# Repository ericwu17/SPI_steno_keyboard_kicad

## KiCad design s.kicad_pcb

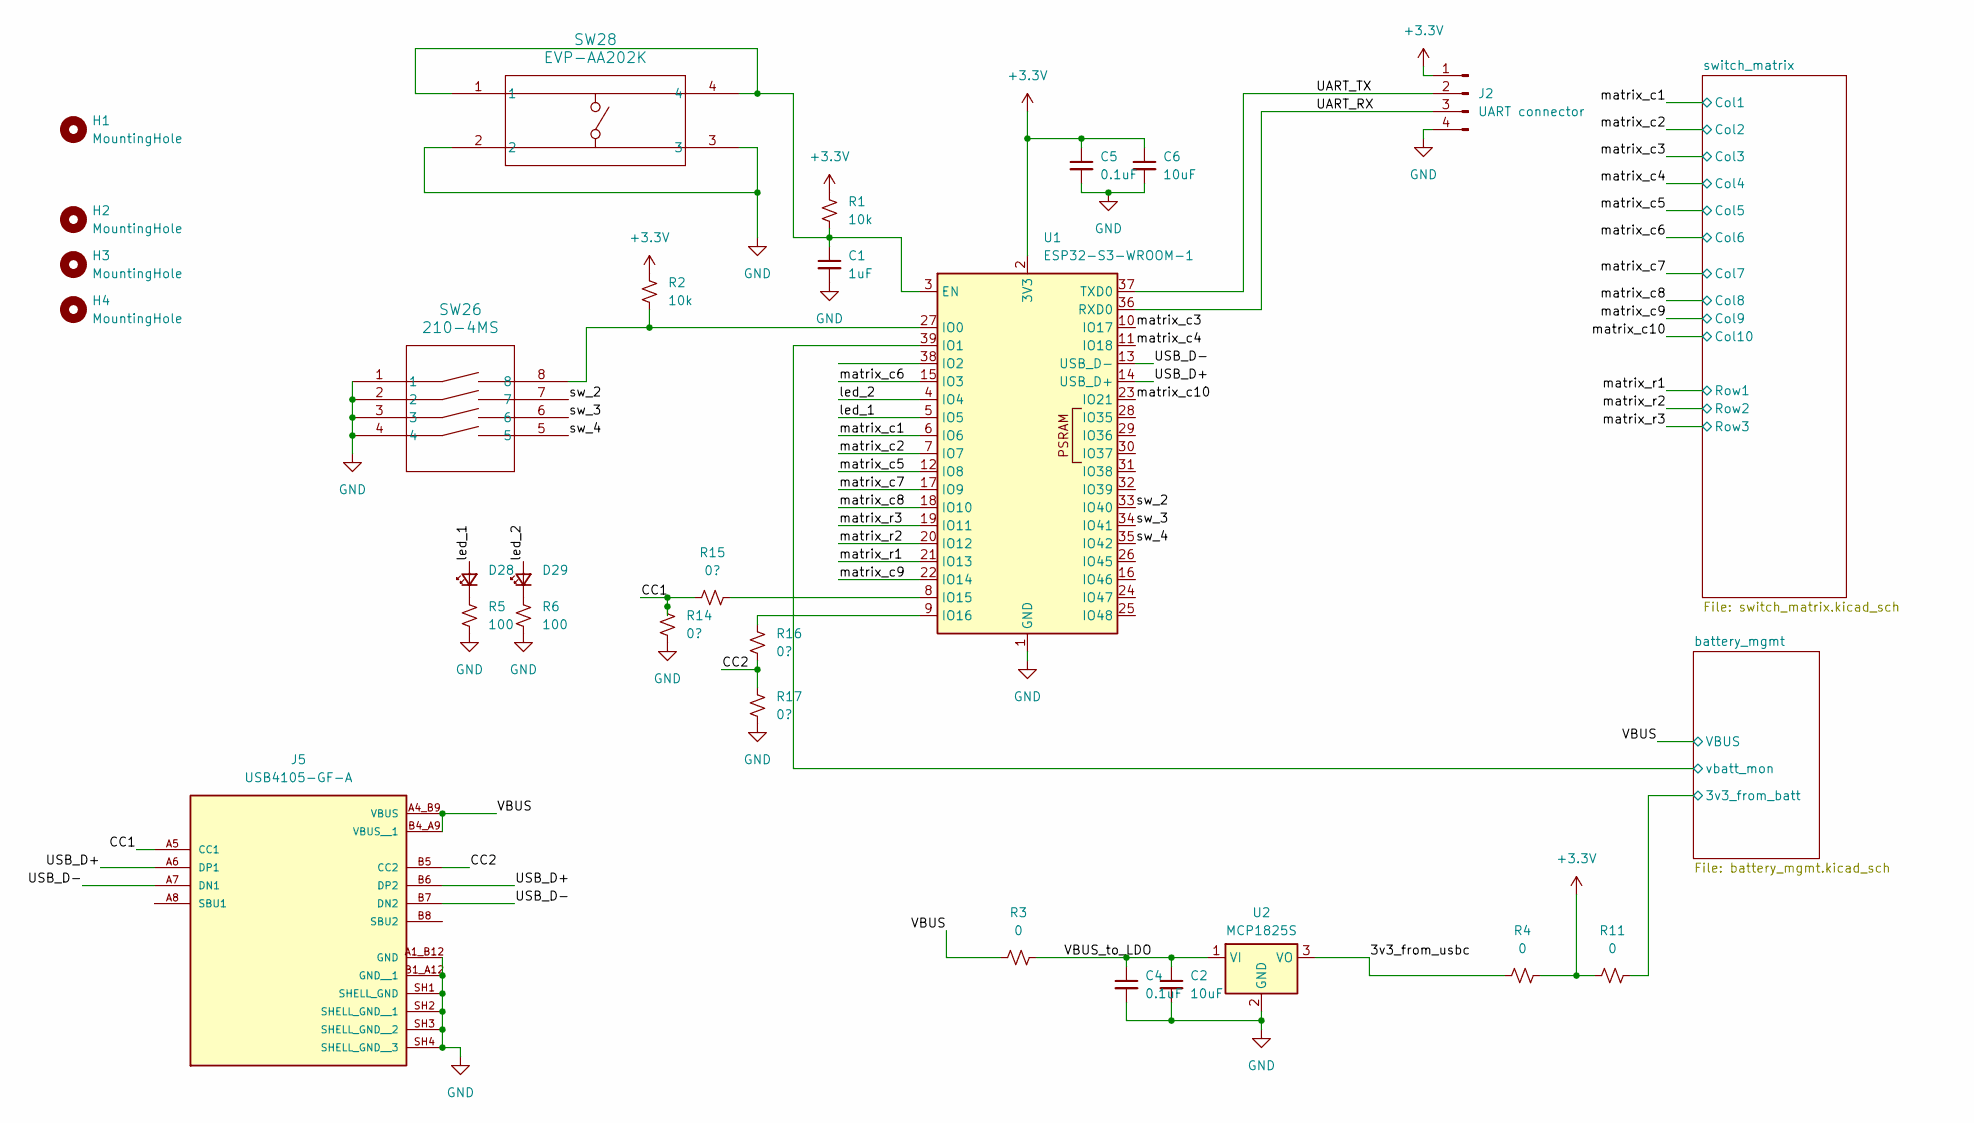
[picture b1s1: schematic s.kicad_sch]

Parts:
C1: 1uF; C_0805_2012Metric_Pad1.18x1.45mm_HandSolder
C2, C6: 10uF; C_0805_2012Metric_Pad1.18x1.45mm_HandSolder
C4, C5: 0.1uF; C_0805_2012Metric_Pad1.18x1.45mm_HandSolder
D28, D29: LED_0805_2012Metric_Pad1.15x1.40mm_HandSolder
H1, H2, H3, H4: MountingHole; MountingHole_3mm
J2: UART connector; PinHeader_1x04_P2.54mm_Vertical
J5: USB4105-GF-A; GCT_USB4105-GF-A; PARTREV B4
R1, R2: 10k; R_0805_2012Metric_Pad1.20x1.40mm_HandSolder
R3, R4, R11: 0; R_0805_2012Metric_Pad1.20x1.40mm_HandSolder
R5, R6: 100; R_0805_2012Metric_Pad1.20x1.40mm_HandSolder
R14, R15, R16, R17: 0?; R_0805_2012Metric_Pad1.20x1.40mm_HandSolder
SW26: 210-4MS; DIP8_210-4_CTS
SW28: EVP-AA202K; SW_EVP-AA102K_PAN
U1: ESP32-S3-WROOM-1
U2: MCP1825S; SOT-223-3_TabPin2

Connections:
+3.3V: C5.1, C6.1, J2.1, R1.1, R2.1, R4.2, R11.1, U1.2 (3V3)
/3v3_from_usbc: R4.1, U2.3 (VO)
/CC1: J5.A5 (CC1), R14.1, R15.1
/CC2: J5.B5 (CC2), R16.1, R17.1
/UART_RX: J2.3, U1.36 (RXD0)
/UART_TX: J2.2, U1.37 (TXD0)
/USB_D+: J5.A6 (DP1), J5.B6 (DP2), U1.14 (USB_D+)
/USB_D-: J5.A7 (DN1), J5.B7 (DN2), U1.13 (USB_D-)
/VBUS: J5.A4_B9 (VBUS), J5.B4_A9 (VBUS__1), R3.1; also elsewhere on the board
/VBUS_to_LDO: C2.1, C4.1, R3.2, U2.1 (VI)
/battery_mgmt/3v3_from_batt: R11.2; also elsewhere on the board
/battery_mgmt/vbatt_mon: U1.39 (IO1); also elsewhere on the board
/led_1: D28.2 (A), U1.5 (IO5)
/led_2: D29.2 (A), U1.4 (IO4)
/matrix_c1: U1.6 (IO6); also elsewhere on the board
/matrix_c2: U1.7 (IO7); also elsewhere on the board
/matrix_c3: U1.10 (IO17); also elsewhere on the board
/matrix_c4: U1.11 (IO18); also elsewhere on the board
/matrix_c5: U1.12 (IO8); also elsewhere on the board
/matrix_c6: U1.15 (IO3); also elsewhere on the board
/matrix_c7: U1.17 (IO9); also elsewhere on the board
/matrix_c8: U1.18 (IO10); also elsewhere on the board
/matrix_c9: U1.22 (IO14); also elsewhere on the board
/matrix_c10: U1.23 (IO21); also elsewhere on the board
/matrix_r1: U1.21 (IO13); also elsewhere on the board
/matrix_r2: U1.20 (IO12); also elsewhere on the board
/matrix_r3: U1.19 (IO11); also elsewhere on the board
/sw_2: SW26.7, U1.33 (IO40)
/sw_3: SW26.6, U1.34 (IO41)
/sw_4: SW26.5, U1.35 (IO42)
GND: C1.2, C2.2, C4.2, C5.2, C6.2, J2.4, J5.A1_B12 (GND), J5.B1_A12 (GND__1), J5.SH1 (SHELL_GND), J5.SH2 (SHELL_GND__1), J5.SH3 (SHELL_GND__2), J5.SH4 (SHELL_GND__3), R5.2, R6.2, R14.2, R17.2, SW26.1, SW26.2, SW26.3, SW26.4, SW28.2, SW28.3, U1.1 (GND), U1.40 (GND), U1.41 (GND), U2.2 (GND); also elsewhere on the board
unnamed: D28.1 (K), R5.1
unnamed: D29.1 (K), R6.1
unnamed: C1.1, R1.2, SW28.1, SW28.4, U1.3 (EN)
unnamed: R2.2, SW26.8, U1.27 (IO0)
unnamed: R15.2, U1.8 (IO15)
unnamed: R16.2, U1.9 (IO16)

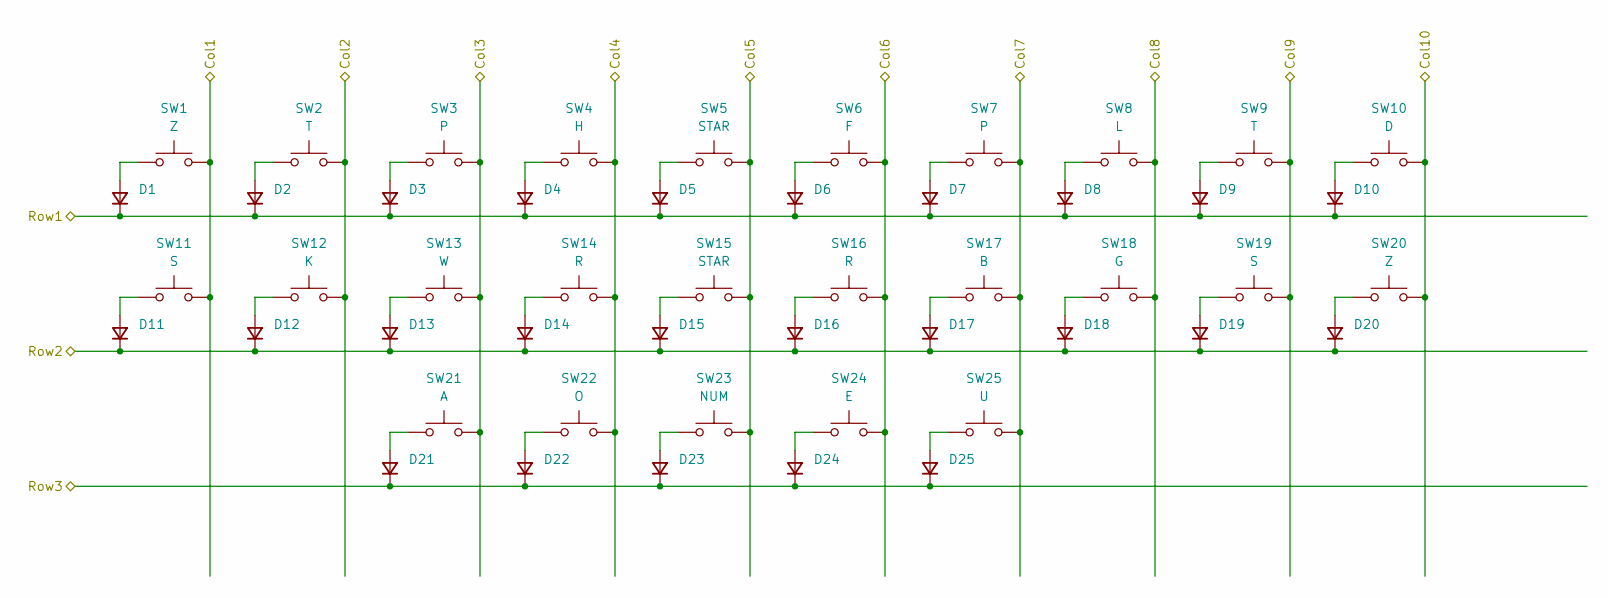
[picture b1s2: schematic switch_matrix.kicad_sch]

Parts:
D1, D2, D3, D4, D5, D6, D7, D8, D9, D10, D11, D12, D13, D14, D15, D16, D17, D18, D19, D20, D21, D22, D23, D24, D25: D_SOD-323_HandSoldering
SW1, SW20: Z; SW_Kailh_Choc_V1_THT
SW2, SW9: T; SW_Kailh_Choc_V1_THT
SW3, SW7: P; SW_Kailh_Choc_V1_THT
SW4: H; SW_Kailh_Choc_V1_THT
SW5, SW15: STAR; SW_Kailh_Choc_V1_THT
SW6: F; SW_Kailh_Choc_V1_THT
SW8: L; SW_Kailh_Choc_V1_THT
SW10: D; SW_Kailh_Choc_V1_THT
SW11, SW19: S; SW_Kailh_Choc_V1_THT
SW12: K; SW_Kailh_Choc_V1_THT
SW13: W; SW_Kailh_Choc_V1_THT
SW14, SW16: R; SW_Kailh_Choc_V1_THT
SW17: B; SW_Kailh_Choc_V1_THT
SW18: G; SW_Kailh_Choc_V1_THT
SW21: A; SW_Kailh_Choc_V1_THT
SW22: O; SW_Kailh_Choc_V1_THT
SW23: NUM; SW_Kailh_Choc_V1_THT
SW24: E; SW_Kailh_Choc_V1_THT
SW25: U; SW_Kailh_Choc_V1_THT

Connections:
/matrix_c1: SW1.2, SW11.2; also elsewhere on the board
/matrix_c2: SW2.2, SW12.2; also elsewhere on the board
/matrix_c3: SW3.2, SW13.2, SW21.2; also elsewhere on the board
/matrix_c4: SW4.2, SW14.2, SW22.2; also elsewhere on the board
/matrix_c5: SW5.2, SW15.2, SW23.2; also elsewhere on the board
/matrix_c6: SW6.2, SW16.2, SW24.2; also elsewhere on the board
/matrix_c7: SW7.2, SW17.2, SW25.2; also elsewhere on the board
/matrix_c8: SW8.2, SW18.2; also elsewhere on the board
/matrix_c9: SW9.2, SW19.2; also elsewhere on the board
/matrix_c10: SW10.2, SW20.2; also elsewhere on the board
/matrix_r1: D1.1 (K), D2.1 (K), D3.1 (K), D4.1 (K), D5.1 (K), D6.1 (K), D7.1 (K), D8.1 (K), D9.1 (K), D10.1 (K); also elsewhere on the board
/matrix_r2: D11.1 (K), D12.1 (K), D13.1 (K), D14.1 (K), D15.1 (K), D16.1 (K), D17.1 (K), D18.1 (K), D19.1 (K), D20.1 (K); also elsewhere on the board
/matrix_r3: D21.1 (K), D22.1 (K), D23.1 (K), D24.1 (K), D25.1 (K); also elsewhere on the board
unnamed: D1.2 (A), SW1.1
unnamed: D2.2 (A), SW2.1
unnamed: D3.2 (A), SW3.1
unnamed: D4.2 (A), SW4.1
unnamed: D5.2 (A), SW5.1
unnamed: D6.2 (A), SW6.1
unnamed: D7.2 (A), SW7.1
unnamed: D8.2 (A), SW8.1
unnamed: D9.2 (A), SW9.1
unnamed: D10.2 (A), SW10.1
unnamed: D11.2 (A), SW11.1
unnamed: D12.2 (A), SW12.1
unnamed: D13.2 (A), SW13.1
unnamed: D14.2 (A), SW14.1
unnamed: D15.2 (A), SW15.1
unnamed: D16.2 (A), SW16.1
unnamed: D17.2 (A), SW17.1
unnamed: D18.2 (A), SW18.1
unnamed: D19.2 (A), SW19.1
unnamed: D20.2 (A), SW20.1
unnamed: D21.2 (A), SW21.1
unnamed: D22.2 (A), SW22.1
unnamed: D23.2 (A), SW23.1
unnamed: D24.2 (A), SW24.1
unnamed: D25.2 (A), SW25.1

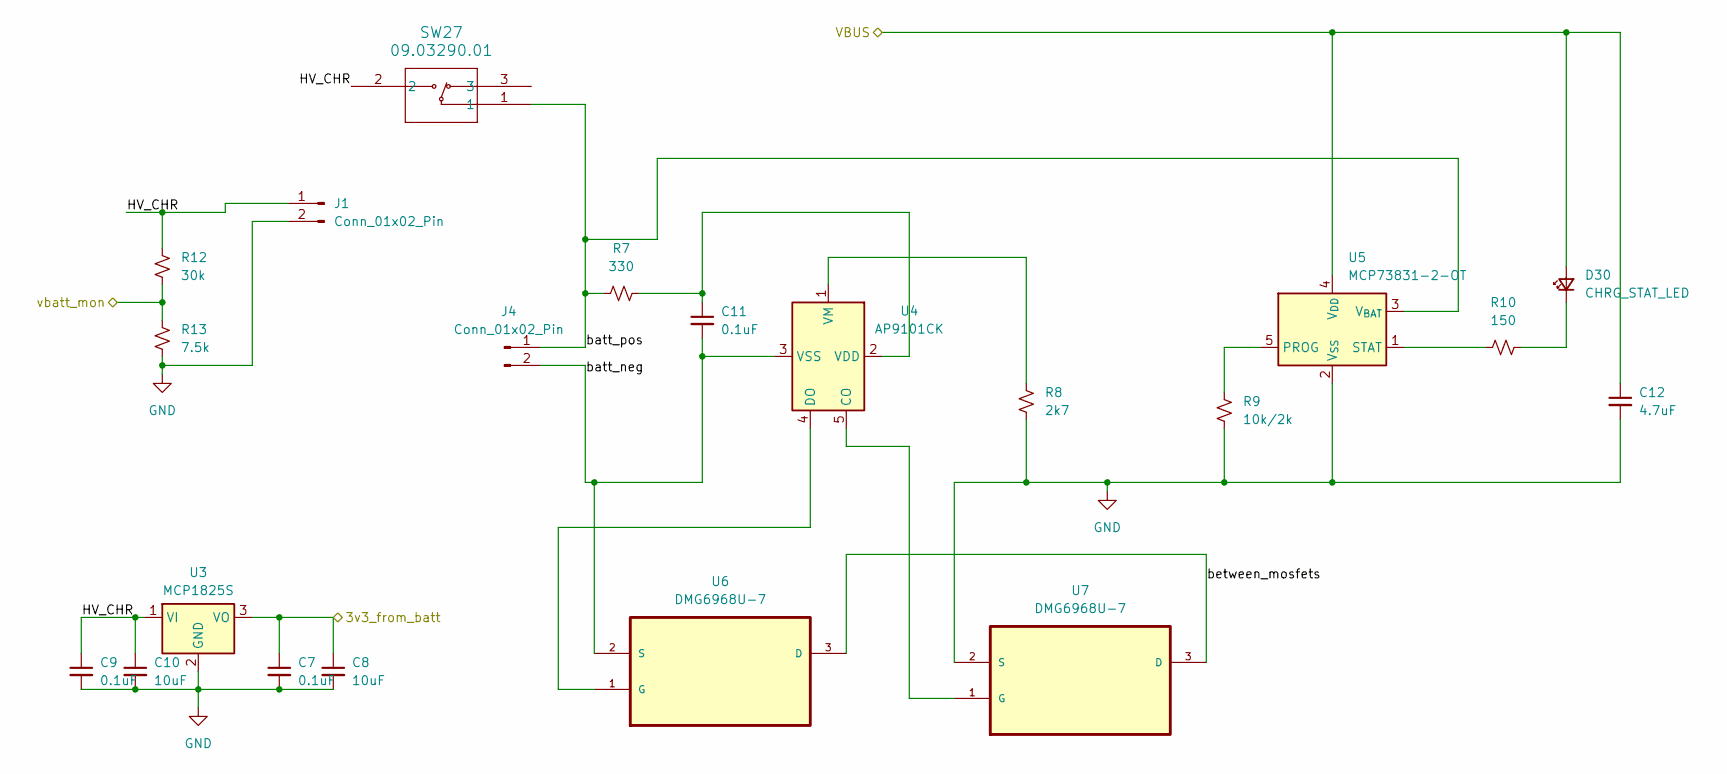
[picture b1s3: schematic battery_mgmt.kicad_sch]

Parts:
C7, C9, C11: 0.1uF; C_0805_2012Metric_Pad1.18x1.45mm_HandSolder
C8, C10: 10uF; C_0805_2012Metric_Pad1.18x1.45mm_HandSolder
C12: 4.7uF; C_0805_2012Metric_Pad1.18x1.45mm_HandSolder
D30: CHRG_STAT_LED; LED_0805_2012Metric_Pad1.15x1.40mm_HandSolder
J1: Conn_01x02_Pin; PinHeader_1x02_P2.54mm_Vertical
J4: Conn_01x02_Pin; JST_PH_S2B-PH-K_1x02_P2.00mm_Horizontal
R7: 330; R_0805_2012Metric_Pad1.20x1.40mm_HandSolder
R8: 2k7; R_0805_2012Metric_Pad1.20x1.40mm_HandSolder
R9: 10k/2k; R_0805_2012Metric_Pad1.20x1.40mm_HandSolder
R10: 150; R_0805_2012Metric_Pad1.20x1.40mm_HandSolder
R12: 30k; R_0805_2012Metric_Pad1.20x1.40mm_HandSolder
R13: 7.5k; R_0805_2012Metric_Pad1.20x1.40mm_HandSolder
SW27: 09.03290.01; 09.03290_EAO
U3: MCP1825S; SOT-223-3_TabPin2
U4: AP9101CK; SOT-23-5
U5: MCP73831-2-OT; SOT-23-5
U6, U7: DMG6968U-7; SOT95P240X110-3N; MPN DMG6968U-7

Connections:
/VBUS: C12.1, D30.2 (A), U5.4 (V_{DD}); also elsewhere on the board
/battery_mgmt/3v3_from_batt: C7.1, C8.1, U3.3 (VO); also elsewhere on the board
/battery_mgmt/HV_CHR: C9.1, C10.1, J1.1, R12.1, SW27.2, U3.1 (VI)
/battery_mgmt/batt_neg: C11.2, J4.2, U4.3 (VSS), U6.2 (S)
/battery_mgmt/batt_pos: J4.1, R7.1, SW27.1, U5.3 (V_{BAT})
/battery_mgmt/between_mosfets: U6.3 (D), U7.3 (D)
/battery_mgmt/vbatt_mon: R12.2, R13.1; also elsewhere on the board
GND: C7.2, C8.2, C9.2, C10.2, C12.2, J1.2, R8.2, R9.2, R13.2, U3.2 (GND), U5.2 (V_{SS}), U7.2 (S); also elsewhere on the board
unnamed: D30.1 (K), R10.2
unnamed: U4.5 (CO), U7.1 (G)
unnamed: U4.4 (DO), U6.1 (G)
unnamed: C11.1, R7.2, U4.2 (VDD)
unnamed: R8.1, U4.1 (VM)
unnamed: R9.1, U5.5 (PROG)
unnamed: R10.1, U5.1 (STAT)

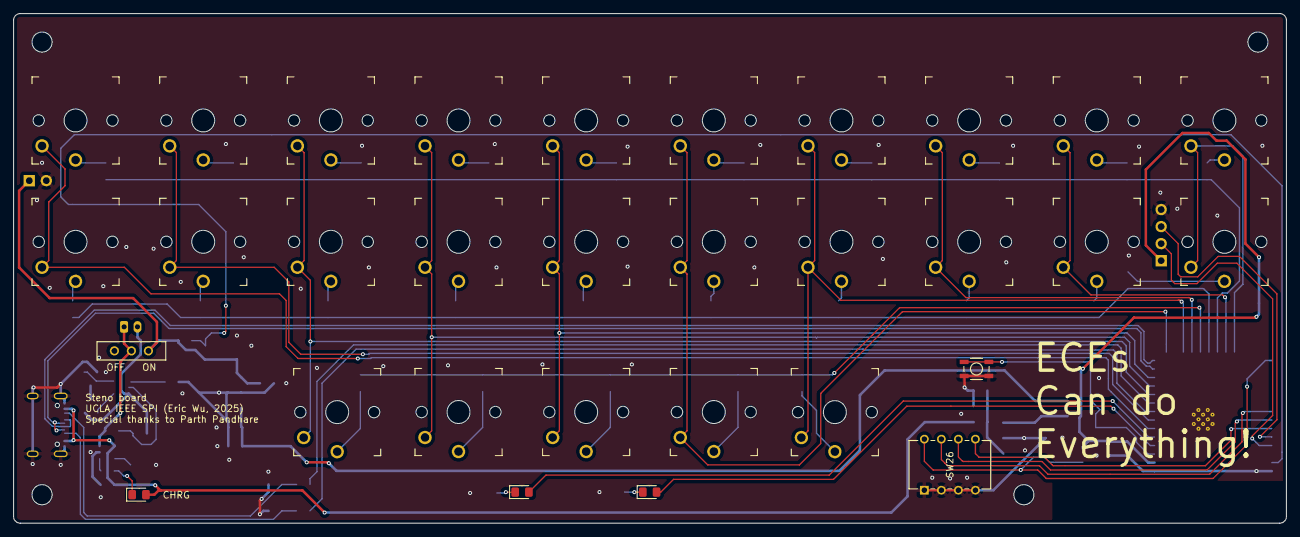
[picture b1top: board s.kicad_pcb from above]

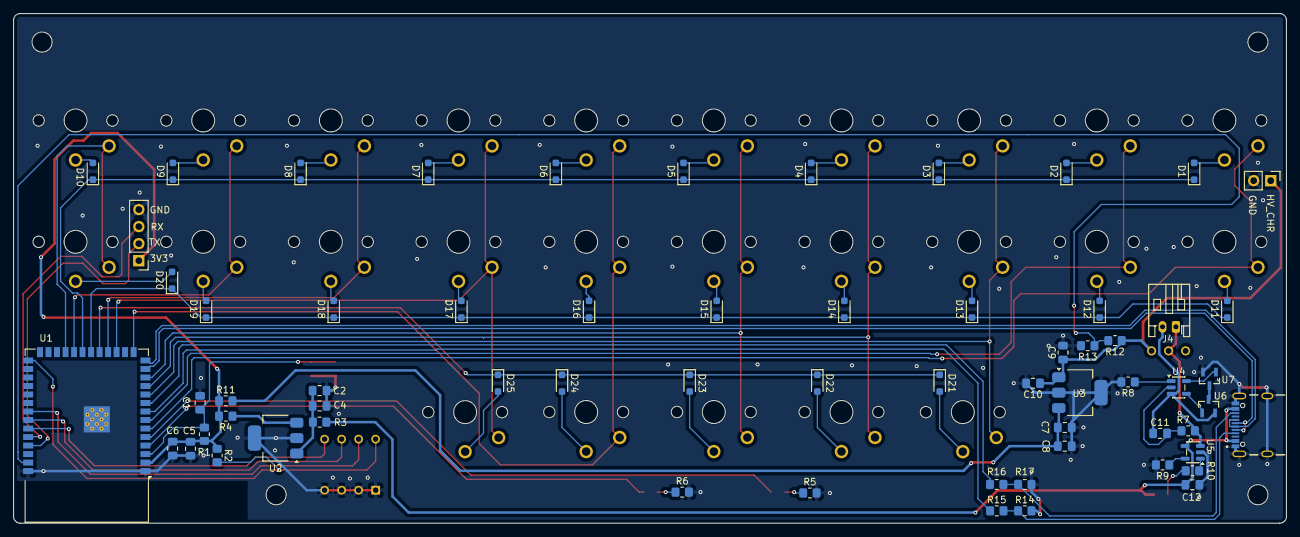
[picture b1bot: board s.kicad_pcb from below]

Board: 2 copper layers, 190.0 x 76.0 mm, 99 parts (64 on the bottom side), 73 nets.

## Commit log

2025-10-25 initial commit: added submodules
2025-10-25 initial commit 2: initialize project
2025-10-25 got basic MCU powering from USBC
2025-10-25 make key matrix
2025-10-25 rename backup, for somme reason
    idk why kicad did this
2025-10-25 connect MCU to matrix
2025-10-26 add supporting stuff and assigned footprints
2025-10-26 copied battery charging schematic
2025-10-26 update footprints
2025-10-26 move stuff around on pcb
2025-10-26 routed the key matrix
2025-10-26 quick commit: moved stuff around and deleted a capacitor
2025-10-26 route some more stuff
2025-10-26 route dip switches
2025-10-26 route battery charging stuff
2025-10-26 move stuff around (minor)
2025-10-27 add submodule for Kailh Choc V1 footprints
2025-10-27 change key footprints to kailh choc (PCB not fixed yet)
2025-10-27 remove 2 of the 4 user LEDs
2025-10-27 PCB cleanup remove old row/col traces
2025-10-28 route PCB with new keys and new key spacing
    key spacing done by hand
2025-10-28 add backups
2025-10-30 modify schematic: add switch between voltage regs
2025-10-30 work on PCB
2025-10-30 more work on PCB: routed grounds
2025-10-30 fix DRC violations and warnings
2025-11-01 use 0-ohm resistors, not switches, to control power source
2025-11-01 add a voltage divider for battery voltage monitoring
2025-11-06 make gap in PCB for antenna
2025-11-06 remove silkscreen from MCU component
2025-11-06 change min hole size to 0.2 mm
2025-11-06 some silk screen changes
2025-11-06 silk screen changes
2025-11-06 new usb port footprint
2025-11-07 change power switch
2025-11-07 minor edit to some traces
2025-11-07 add design rules from https://github.com/labtroll/KiCad-DesignRules
2025-11-07 update silk screen to confrom to design rules
2025-11-07 reroute board
2025-11-07 add planes for ground
2025-11-07 add 3 of 4 mounting holes
    still need to think about the last one...
2025-11-08 add the fourth mounting hole
2025-11-08 add a few vias
2025-11-13 add a push button for RST
2025-11-16 change footprint of JST connector. Vertical -> horizontal
2025-11-18 rename labels for mounting holes
2025-11-18 WIP: drafting PCB edges
2025-11-18 WIP :finalize edge cuts
    The new board dimensions are 189.95mm x 76.05mm
    with corners of radius 1.00 mm
2025-11-18 WIP: routing traces
2025-11-18 WIP: more routing done
2025-11-18 WIP: route everything except ground planes
2025-11-18 add fill zones for GND
2025-11-18 add some vias
2025-11-18 refill all zones
2025-11-18 update footprints from libraries
2025-11-18 move silkscreen (was intersecting with vias)
2025-11-19 add a test point for battery voltage
